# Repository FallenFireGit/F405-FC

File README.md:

# F405-FC

STM32F405 flight controller for 30.5 mm quadcopter stacks. 2–6S input, dual IMU, Betaflight and INAV targets. Every part is sourced from DigiKey.

| Top | Bottom |
|---|---|
|  |  |

> **Status: rev D, design complete, not yet built.** DRC and ERC are clean, and every review gate's major findings are fixed and re-reviewed. Nothing has been fabricated, powered or flashed yet. See [review/summary.md](review/summary.md) for open risks and the list of what wasn't verified.

## Specs

| | |
|---|---|
| MCU | STM32F405RGT6, 168 MHz, LQFP-64 |
| IMUs | ICM-42688-P + BMI270 (SPI1, separate CS and INT) |
| Barometer | BMP390 (I2C1) |
| Magnetometer | IIS2MDC (I2C1), plus external I2C on the GPS port |
| Blackbox | W25N01GV, 1 Gbit SPI NAND |
| Input | 2–6S, SMBJ26A TVS, VBAT/GND solder pads |
| Regulators | 2× LMR38020 synchronous buck (5 V, and 10 V switchable for VTX pit mode), LP38692 3.3 V, LP5907 low-noise 3.3 V for the IMUs |
| Video | HD digital VTX port (MSP DisplayPort OSD) on a JST-SH 6-pin, analog camera switch (TS5A3159A) between two cameras |
| Outputs | 8 motor/servo outputs (M1–M4 on the ESC connector support bidirectional DShot), WS2812 LED strip, buzzer |
| I/O | 6 UARTs, USB-C (USB 2.0 FS, ESD protected), JST-SH ESC 8-pin, GPS 6-pin, ELRS 4-pin |
| Board | 36 × 36 mm, 30.5 mm M3 mounting, 6 layers (solid GND on In1/In4), 1.6 mm |
| Assembly | Hand / hot-air with stencil, 0402 minimum, no BGA |

There's no analog OSD. The AT7456E has no DigiKey listing and the MAX7456 is obsolete, so OSD comes over MSP DisplayPort (see [D-01](design/decisions.md)).

## Repository layout

| Path | Contents |
|---|---|
| `kicad/` | KiCad 10 project: hierarchical schematic, board, design rules |
| `fab/` | JLCPCB Gerber/drill zip, stencil, placement (CPL) files |
| `bom/` | DigiKey BOM Manager CSV, costed BOM (~$173 for 2 boards plus spares), interactive HTML BOM |
| `docs/` | Schematic PDF, STEP, renders, Betaflight config, INAV target, [assembly and bring-up guide](docs/assembly_and_bringup.md) |
| `design/` | Requirements, pin map and DMA plan, power design, decision log |
| `review/` | Reports from each review gate (pin map, power, schematic, sourcing, footprints, placement, SI/PI, DFM, red team) |
| `gen/` | Python generators: circuit model → schematic → board, routing helpers, checks |
| `lib/` | Custom footprints |

## How it was made

The design was generated from a Python circuit model (`gen/`) into KiCad 10. It was routed with a mix of scripted critical routes and Freerouting. It then went through staged reviews, each done by independent agents told to assume mistakes exist and to cite evidence:

0. pin map and power
1. schematic
2. sourcing and footprints
3. placement
4. signal and power integrity
5. manufacturability
6. two red teams (first power-up and Betaflight bring-up)

Each gate looped through fixes and re-review until no blocking or major findings remained. The previous 4-layer rev C is kept on branch [`rev-c`](../../tree/rev-c); it isn't recommended.

## Before ordering

- Upload `bom/F405FC_digikey_bom.csv` to DigiKey's BOM Manager to confirm live stock and prices. Stock was checked only through dated web snapshots.
- Choose the JLCPCB 6-layer stackup and order **epoxy-filled, capped vias (POFV)**, since some vias are in or next to pads.
- Follow the bring-up guide: check the rails on a current-limited supply before fitting the MCU.

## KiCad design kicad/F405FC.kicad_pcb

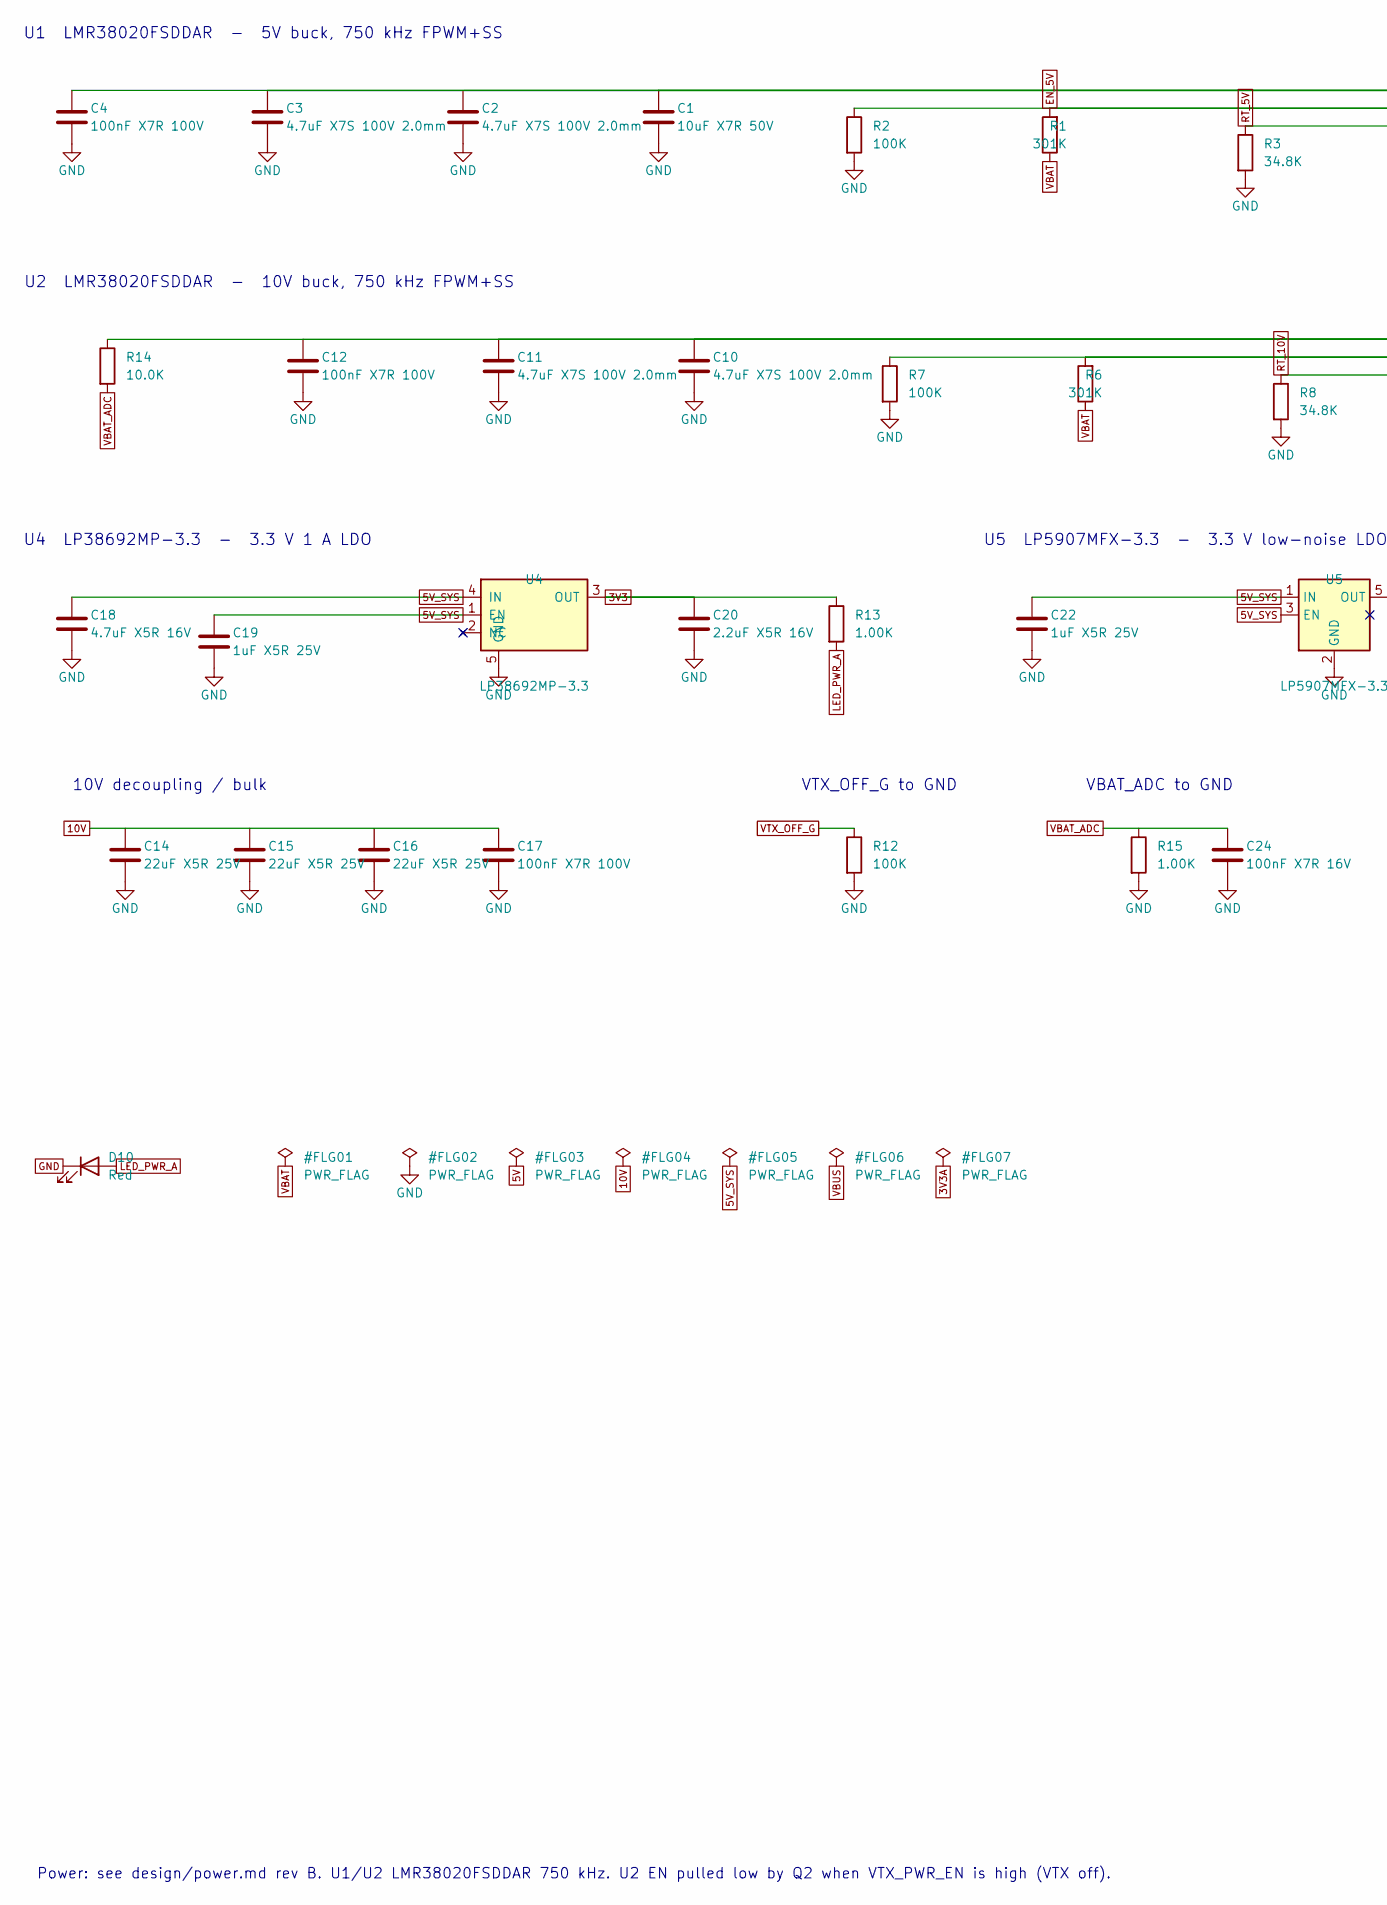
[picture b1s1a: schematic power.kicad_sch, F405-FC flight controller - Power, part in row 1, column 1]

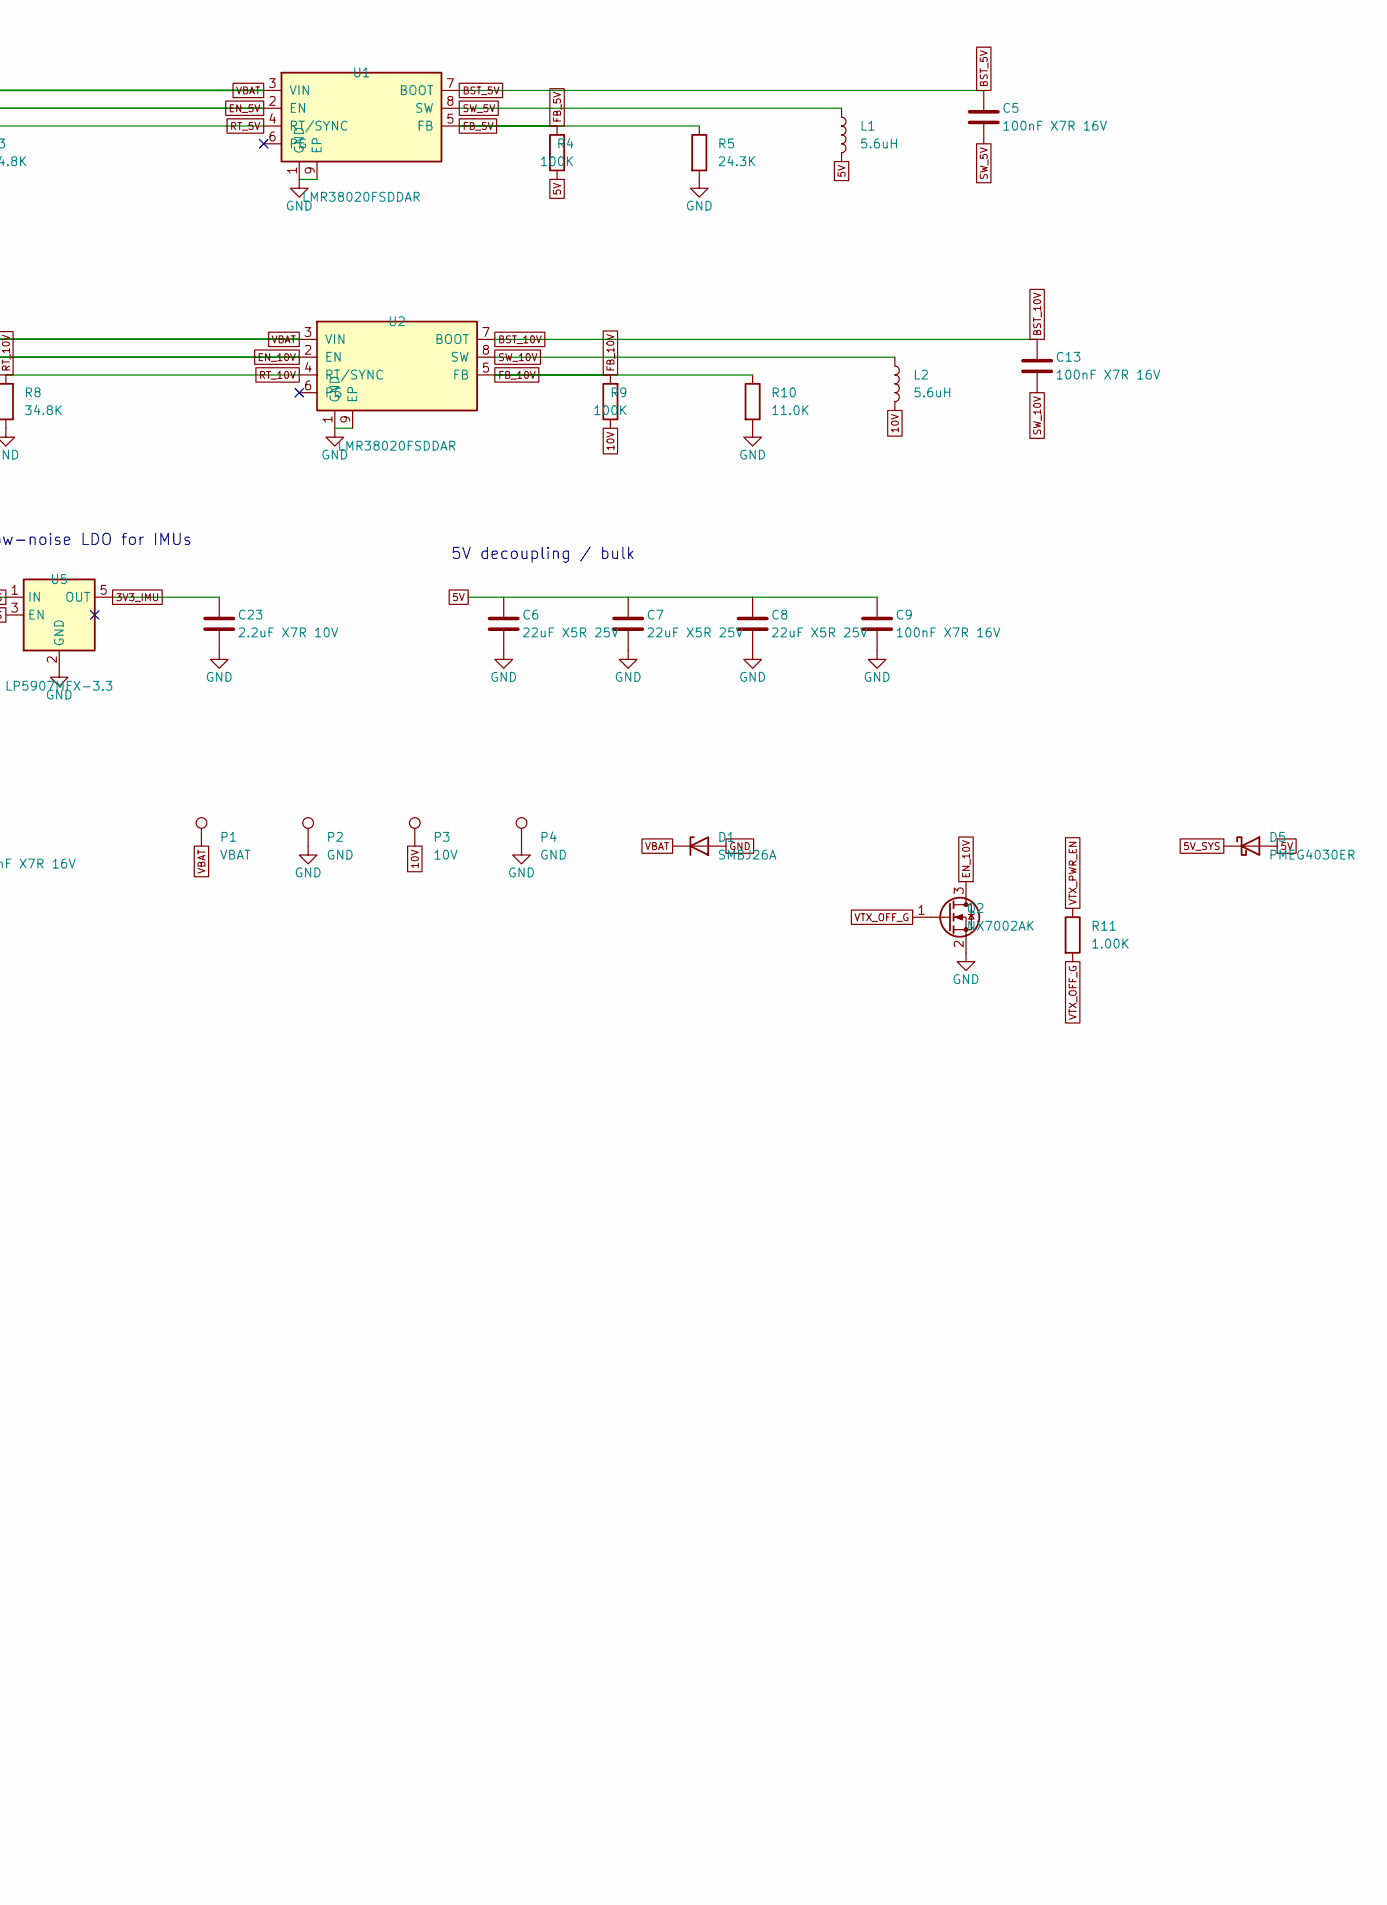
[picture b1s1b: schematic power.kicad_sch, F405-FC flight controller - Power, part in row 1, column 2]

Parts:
C1: 10uF X7R 50V; C_1210_3225Metric; MPN CL32B106KBJNNNE; DigiKey 1276-3387-1-ND
C2, C3, C10, C11: 4.7uF X7S 100V 2.0mm; C_1210_3225Metric; MPN C3225X7S2A475K200AB; DigiKey 445-6042-1-ND (verify: K200AB cut tape)
C4, C12, C17: 100nF X7R 100V; C_0603_1608Metric; MPN GRM188R72A104KA35D; DigiKey 490-3285-1-ND (verify)
C5, C9, C13, C24: 100nF X7R 16V; C_0402_1005Metric; MPN CL05B104KO5NNNC; DigiKey 1276-1001-1-ND
C6, C7, C8, C14, C15, C16: 22uF X5R 25V; C_1206_3216Metric; MPN CL31A226KAHNNNE; DigiKey 1276-3047-1-ND
C18: 4.7uF X5R 16V; C_0603_1608Metric; MPN CL10A475KO8NNNC; DigiKey 1276-1784-1-ND
C19, C22: 1uF X5R 25V; C_0603_1608Metric; MPN CL10A105KA8NNNC; DigiKey 1276-1102-1-ND (verify)
C20: 2.2uF X5R 16V; C_0603_1608Metric; MPN CL10A225KO8NNNC; DigiKey 1276-1040-1-ND
C23: 2.2uF X7R 10V; C_0603_1608Metric; MPN CL10B225KP8NNNC; DigiKey 1276-1134-1-ND
D1: SMBJ26A; D_SMB; MPN SMBJ26A; DigiKey SMBJ26ALFCT-ND
D5: PMEG4030ER; Nexperia_CFP3_SOD-123W; MPN PMEG4030ER,115; DigiKey 1727-5313-1-ND
D10: Red; LED_0603_1608Metric; MPN LTST-C191KRKT; DigiKey 160-1447-1-ND
L1, L2: 5.6uH; L_Wuerth_MAPI-4020; MPN 78438356056; DigiKey 732-11317-1-ND
P1: VBAT; Pad_SMD_2.5x4.0mm; MPN n/a (PCB pad); DigiKey n/a (PCB pad)
P2: GND; Pad_SMD_2.5x4.0mm; MPN n/a (PCB pad); DigiKey n/a (PCB pad)
P3: 10V; Pad_SMD_2.0x3.0mm; MPN n/a (PCB pad); DigiKey n/a (PCB pad)
P4: GND; Pad_SMD_2.0x3.0mm; MPN n/a (PCB pad); DigiKey n/a (PCB pad)
Q2: NX7002AK; SOT-23; MPN NX7002AK,215; DigiKey 1727-1289-1-ND
R1, R6: 301K; R_0603_1608Metric; MPN RC0603FR-07301KL; DigiKey 311-301KHRCT-ND
R2, R4, R7, R9, R12: 100K; R_0402_1005Metric; MPN RC0402FR-07100KL; DigiKey 311-100KLRCT-ND
R3, R8: 34.8K; R_0402_1005Metric; MPN ERJ-2RKF3482X; DigiKey P34.8KLCT-ND
R5: 24.3K; R_0402_1005Metric; MPN ERJ-2RKF2432X; DigiKey P24.3KLCT-ND
R10: 11.0K; R_0402_1005Metric; MPN RC0402FR-0711KL; DigiKey 311-11.0KLRCT-ND
R11, R13, R15: 1.00K; R_0402_1005Metric; MPN RC0402FR-071KL; DigiKey 311-1.00KLRCT-ND
R14: 10.0K; R_0603_1608Metric; MPN RC0603FR-0710KL; DigiKey 311-10.0KHRCT-ND
U1, U2: LMR38020FSDDAR; TI_HSOIC-8-1EP_3.9x4.9mm_P1.27mm_EP2.71x3.4mm_DDA; MPN LMR38020FSDDAR; DigiKey 296-LMR38020FSDDARCT-ND (verify)
U4: LP38692MP-3.3; SOT-223-5; MPN LP38692MP-3.3/NOPB; DigiKey LP38692MP-3.3/NOPBCT-ND
U5: LP5907MFX-3.3; SOT-23-5; MPN LP5907MFX-3.3/NOPB; DigiKey 296-38557-1-ND

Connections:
3V3: C20.1, R13.1, U4.3 (OUT); also elsewhere on the board
3V3_IMU: C23.1, U5.5 (OUT); also elsewhere on the board
5V: C6.1, C7.1, C8.1, C9.1, D5.2 (A), L1.2, R4.1; also elsewhere on the board
5V_SYS: C18.1, C19.1, C22.1, D5.1 (K), U4.1 (EN), U4.4 (IN), U5.1 (IN), U5.3 (EN); also elsewhere on the board
10V: C14.1, C15.1, C16.1, C17.1, L2.2, P3.1, R9.1; also elsewhere on the board
BST_5V: C5.1, U1.7 (BOOT)
BST_10V: C13.1, U2.7 (BOOT)
EN_5V: R1.2, R2.1, U1.2 (EN)
EN_10V: Q2.3 (D), R6.2, R7.1, U2.2 (EN)
FB_5V: R4.2, R5.1, U1.5 (FB)
FB_10V: R9.2, R10.1, U2.5 (FB)
GND: C1.2, C2.2, C3.2, C4.2, C6.2, C7.2, C8.2, C9.2, C10.2, C11.2, C12.2, C14.2, C15.2, C16.2, C17.2, C18.2, C19.2, C20.2, C22.2, C23.2, C24.2, D1.2 (A), D10.1 (K), P2.1, P4.1, Q2.2 (S), R2.2, R3.2, R5.2, R7.2, R8.2, R10.2, R12.2, R15.2, U1.1 (GND), U1.9 (EP), U2.1 (GND), U2.9 (EP), U4.5 (GND), U5.2 (GND); also elsewhere on the board
LED_PWR_A: D10.2 (A), R13.2
RT_5V: R3.1, U1.4 (RT/SYNC)
RT_10V: R8.1, U2.4 (RT/SYNC)
SW_5V: C5.2, L1.1, U1.8 (SW)
SW_10V: C13.2, L2.1, U2.8 (SW)
VBAT: C1.1, C2.1, C3.1, C4.1, C10.1, C11.1, C12.1, D1.1 (K), P1.1, R1.1, R6.1, R14.1, U1.3 (VIN), U2.3 (VIN); also elsewhere on the board
VBAT_ADC: C24.1, R14.2, R15.1; also elsewhere on the board
VTX_OFF_G: Q2.1 (G), R11.2, R12.1
VTX_PWR_EN: R11.1; also elsewhere on the board

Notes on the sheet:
U1 LMR38020FSDDAR - 5V buck, 750 kHz FPWM+SS
U2 LMR38020FSDDAR - 10V buck, 750 kHz FPWM+SS
U4 LP38692MP-3.3 - 3.3 V 1 A LDO
U5 LP5907MFX-3.3 - 3.3 V low-noise LDO for IMUs
5V decoupling / bulk
10V decoupling / bulk
VTX_OFF_G to GND
VBAT_ADC to GND
Power: see design/power.md rev B. U1/U2 LMR38020FSDDAR 750 kHz. U2 EN pulled low by Q2 when VTX_PWR_EN is high (VTX off).

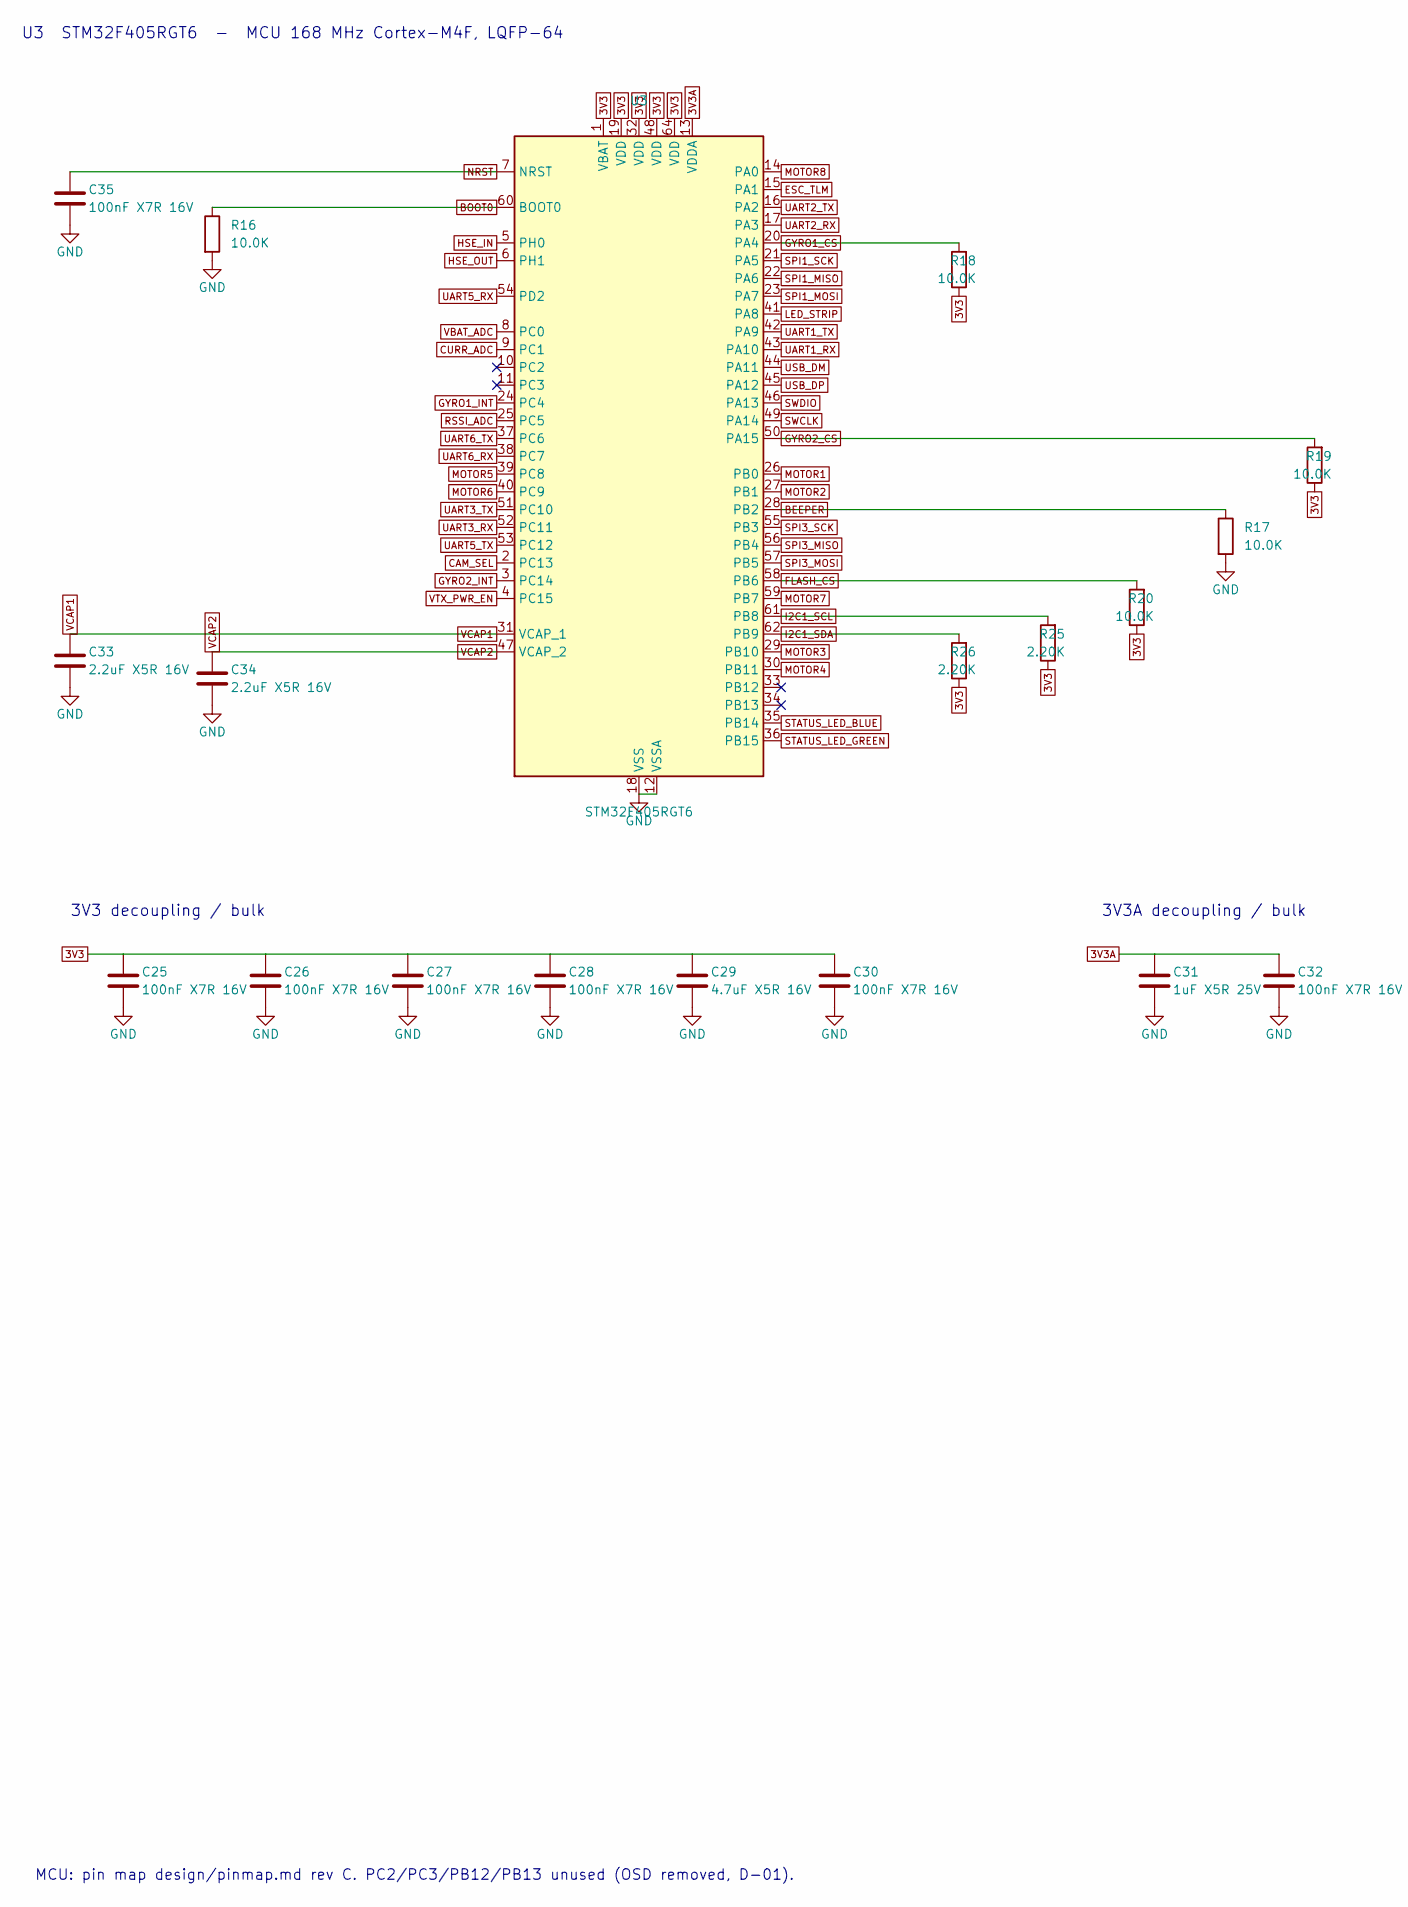
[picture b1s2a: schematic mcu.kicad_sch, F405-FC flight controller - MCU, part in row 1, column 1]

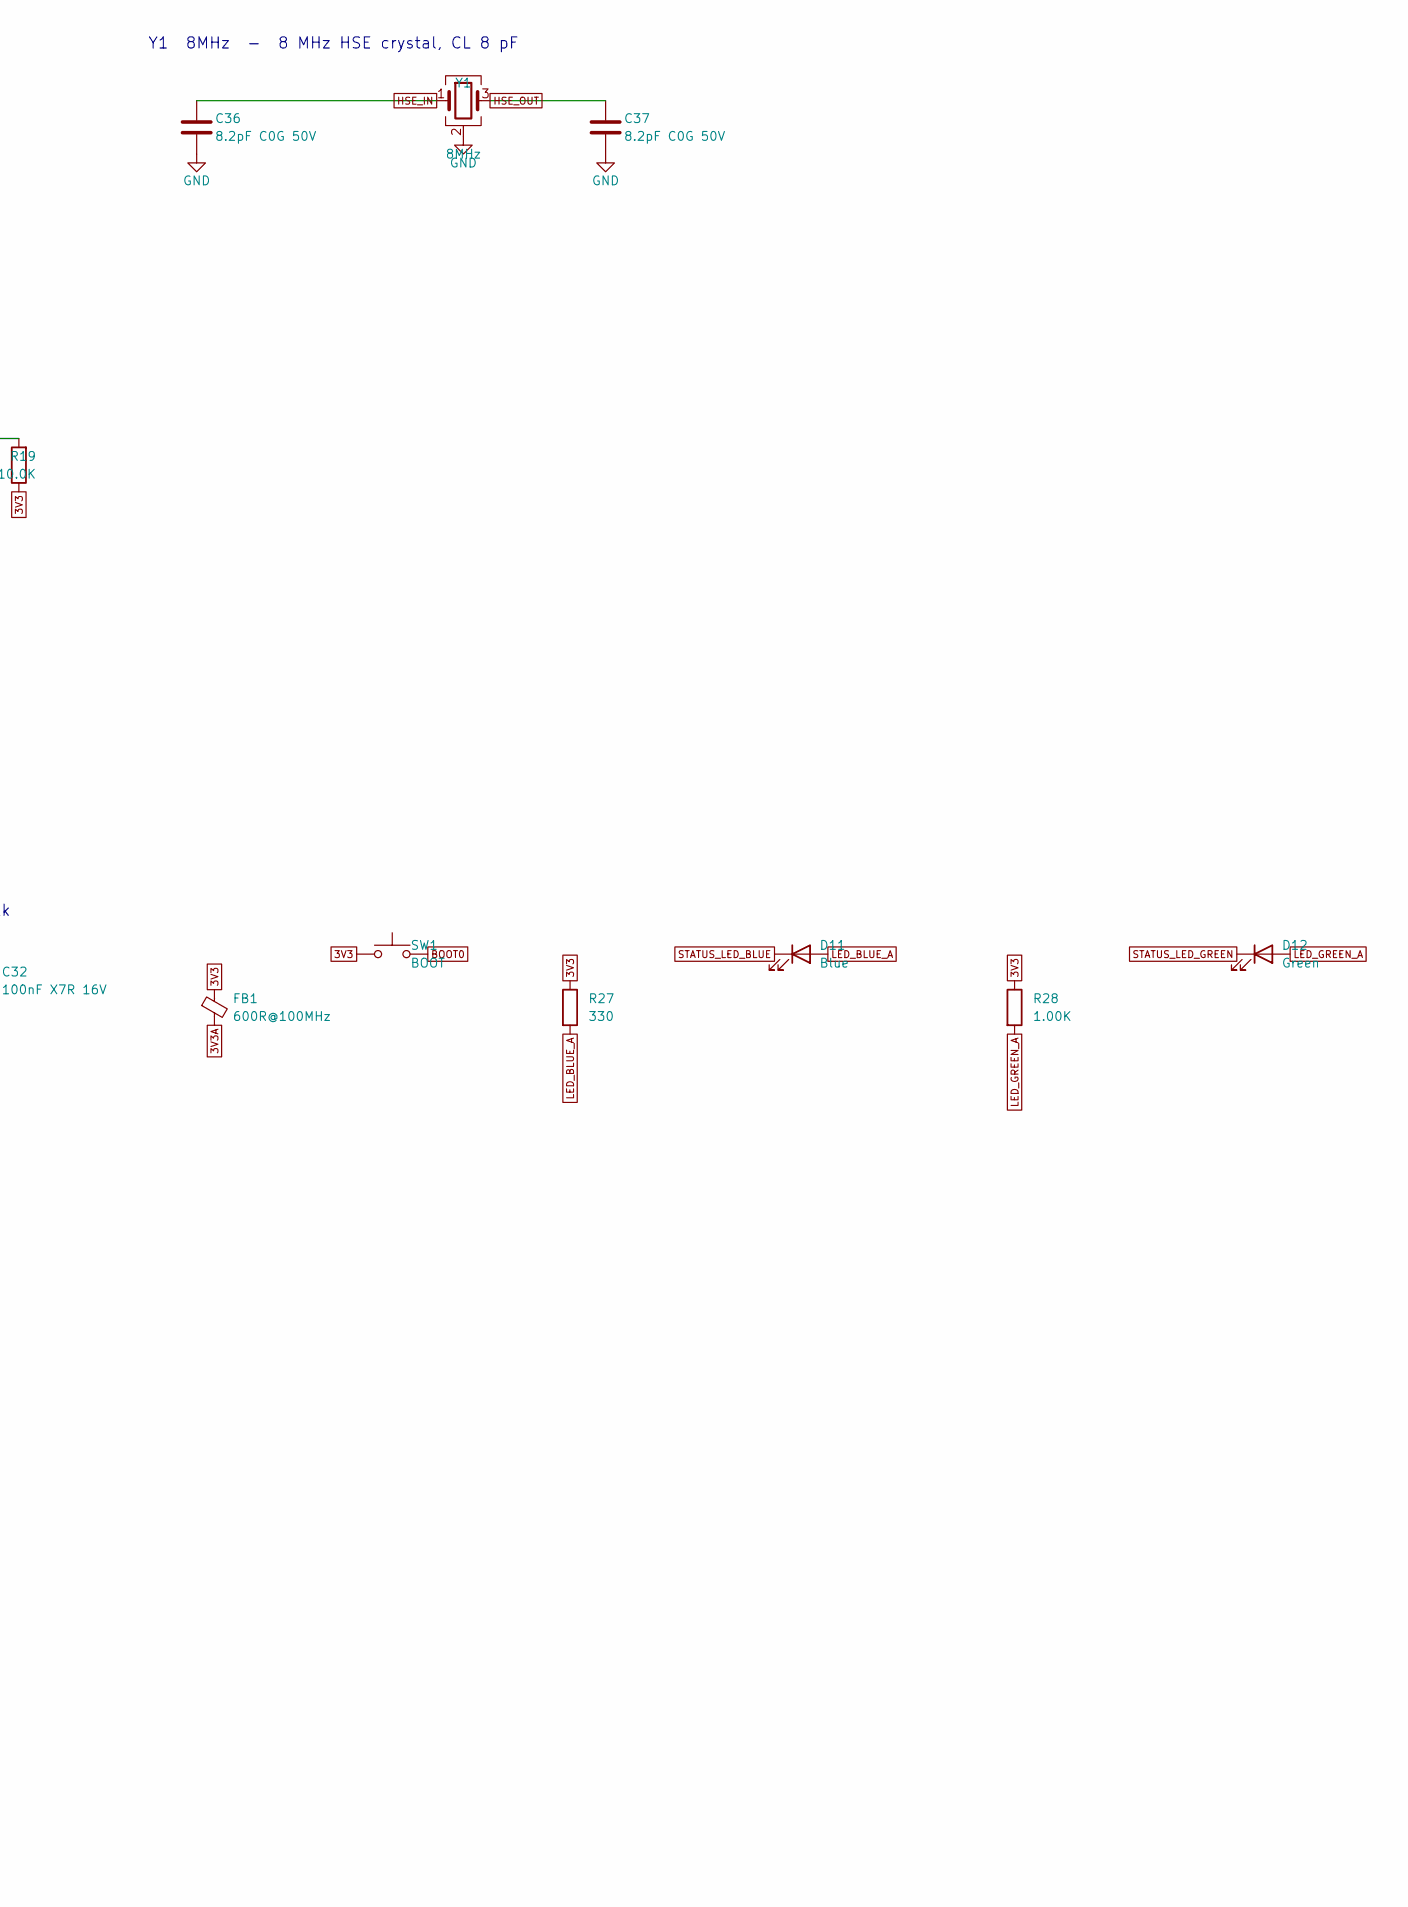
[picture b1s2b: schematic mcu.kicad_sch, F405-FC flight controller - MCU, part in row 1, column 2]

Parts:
C25, C26, C27, C28, C30, C32, C35: 100nF X7R 16V; C_0402_1005Metric; MPN CL05B104KO5NNNC; DigiKey 1276-1001-1-ND
C29: 4.7uF X5R 16V; C_0603_1608Metric; MPN CL10A475KO8NNNC; DigiKey 1276-1784-1-ND
C31: 1uF X5R 25V; C_0603_1608Metric; MPN CL10A105KA8NNNC; DigiKey 1276-1102-1-ND (verify)
C33, C34: 2.2uF X5R 16V; C_0603_1608Metric; MPN CL10A225KO8NNNC; DigiKey 1276-1040-1-ND
C36, C37: 8.2pF C0G 50V; C_0402_1005Metric; MPN C0402C829C5GACTU; DigiKey 399-C0402C829C5GACTUCT-ND
D11: Blue; LED_0603_1608Metric; MPN LTST-C191TBKT; DigiKey 160-1647-1-ND
D12: Green; LED_0603_1608Metric; MPN LTST-C191KGKT; DigiKey 160-1446-1-ND
FB1: 600R@100MHz; L_0603_1608Metric; MPN BLM18KG601SN1D; DigiKey 490-5258-1-ND
R16, R17, R18, R19, R20: 10.0K; R_0402_1005Metric; MPN RC0402FR-0710KL; DigiKey 311-10.0KLRCT-ND
R25, R26: 2.20K; R_0402_1005Metric; MPN RC0402FR-072K2L; DigiKey 311-2.20KLRCT-ND
R27: 330; R_0402_1005Metric; MPN RC0402FR-07330RL; DigiKey 311-330LRCT-ND
R28: 1.00K; R_0402_1005Metric; MPN RC0402FR-071KL; DigiKey 311-1.00KLRCT-ND
SW1: BOOT; SW_SPST_PTS810; MPN PTS810 SJM 250 SMTR LFS; DigiKey CKN10502CT-ND
U3: STM32F405RGT6; LQFP-64_10x10mm_P0.5mm; MPN STM32F405RGT6; DigiKey 497-11767-ND
Y1: 8MHz; Crystal_SMD_3225-4Pin_3.2x2.5mm; MPN ECS-80-8-33-JEN-TR3; DigiKey 50-ECS-80-8-33-JEN-TR3CT-ND

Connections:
3V3: C25.1, C26.1, C27.1, C28.1, C29.1, C30.1, FB1.1, R18.1, R19.1, R20.1, R25.1, R26.1, R27.1, R28.1, SW1.1, U3.1 (VBAT), U3.19 (VDD), U3.32 (VDD), U3.48 (VDD), U3.64 (VDD); also elsewhere on the board
3V3A: C31.1, C32.1, FB1.2, U3.13 (VDDA)
BEEPER: R17.1, U3.28 (PB2); also elsewhere on the board
BOOT0: R16.1, SW1.2, U3.60 (BOOT0)
CAM_SEL: U3.2 (PC13); also elsewhere on the board
CURR_ADC: U3.9 (PC1); also elsewhere on the board
ESC_TLM: U3.15 (PA1); also elsewhere on the board
FLASH_CS: R20.2, U3.58 (PB6); also elsewhere on the board
GND: C25.2, C26.2, C27.2, C28.2, C29.2, C30.2, C31.2, C32.2, C33.2, C34.2, C35.2, C36.2, C37.2, R16.2, R17.2, U3.12 (VSSA), U3.18 (VSS), U3.63 (VSS), Y1.2 (G), Y1.4 (G); also elsewhere on the board
GYRO1_CS: R18.2, U3.20 (PA4); also elsewhere on the board
GYRO1_INT: U3.24 (PC4); also elsewhere on the board
GYRO2_CS: R19.2, U3.50 (PA15); also elsewhere on the board
GYRO2_INT: U3.3 (PC14); also elsewhere on the board
HSE_IN: C36.1, U3.5 (PH0), Y1.1
HSE_OUT: C37.1, U3.6 (PH1), Y1.3
I2C1_SCL: R25.2, U3.61 (PB8); also elsewhere on the board
I2C1_SDA: R26.2, U3.62 (PB9); also elsewhere on the board
LED_BLUE_A: D11.2 (A), R27.2
LED_GREEN_A: D12.2 (A), R28.2
LED_STRIP: U3.41 (PA8); also elsewhere on the board
MOTOR1: U3.26 (PB0); also elsewhere on the board
MOTOR2: U3.27 (PB1); also elsewhere on the board
MOTOR3: U3.29 (PB10); also elsewhere on the board
MOTOR4: U3.30 (PB11); also elsewhere on the board
MOTOR5: U3.39 (PC8); also elsewhere on the board
MOTOR6: U3.40 (PC9); also elsewhere on the board
MOTOR7: U3.59 (PB7); also elsewhere on the board
MOTOR8: U3.14 (PA0); also elsewhere on the board
NRST: C35.1, U3.7 (NRST); also elsewhere on the board
RSSI_ADC: U3.25 (PC5); also elsewhere on the board
SPI1_MISO: U3.22 (PA6); also elsewhere on the board
SPI1_MOSI: U3.23 (PA7); also elsewhere on the board
SPI1_SCK: U3.21 (PA5); also elsewhere on the board
SPI3_MISO: U3.56 (PB4); also elsewhere on the board
SPI3_MOSI: U3.57 (PB5); also elsewhere on the board
SPI3_SCK: U3.55 (PB3); also elsewhere on the board
STATUS_LED_BLUE: D11.1 (K), U3.35 (PB14)
STATUS_LED_GREEN: D12.1 (K), U3.36 (PB15)
SWCLK: U3.49 (PA14); also elsewhere on the board
SWDIO: U3.46 (PA13); also elsewhere on the board
UART1_RX: U3.43 (PA10); also elsewhere on the board
UART1_TX: U3.42 (PA9); also elsewhere on the board
UART2_RX: U3.17 (PA3); also elsewhere on the board
UART2_TX: U3.16 (PA2); also elsewhere on the board
UART3_RX: U3.52 (PC11); also elsewhere on the board
UART3_TX: U3.51 (PC10); also elsewhere on the board
UART5_RX: U3.54 (PD2); also elsewhere on the board
UART5_TX: U3.53 (PC12); also elsewhere on the board
UART6_RX: U3.38 (PC7); also elsewhere on the board
UART6_TX: U3.37 (PC6); also elsewhere on the board
USB_DM: U3.44 (PA11); also elsewhere on the board
USB_DP: U3.45 (PA12); also elsewhere on the board
VBAT_ADC: U3.8 (PC0); also elsewhere on the board
VCAP1: C33.1, U3.31 (VCAP_1)
VCAP2: C34.1, U3.47 (VCAP_2)
VTX_PWR_EN: U3.4 (PC15); also elsewhere on the board

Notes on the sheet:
U3 STM32F405RGT6 - MCU 168 MHz Cortex-M4F, LQFP-64
Y1 8MHz - 8 MHz HSE crystal, CL 8 pF
3V3 decoupling / bulk
3V3A decoupling / bulk
MCU: pin map design/pinmap.md rev C. PC2/PC3/PB12/PB13 unused (OSD removed, D-01).

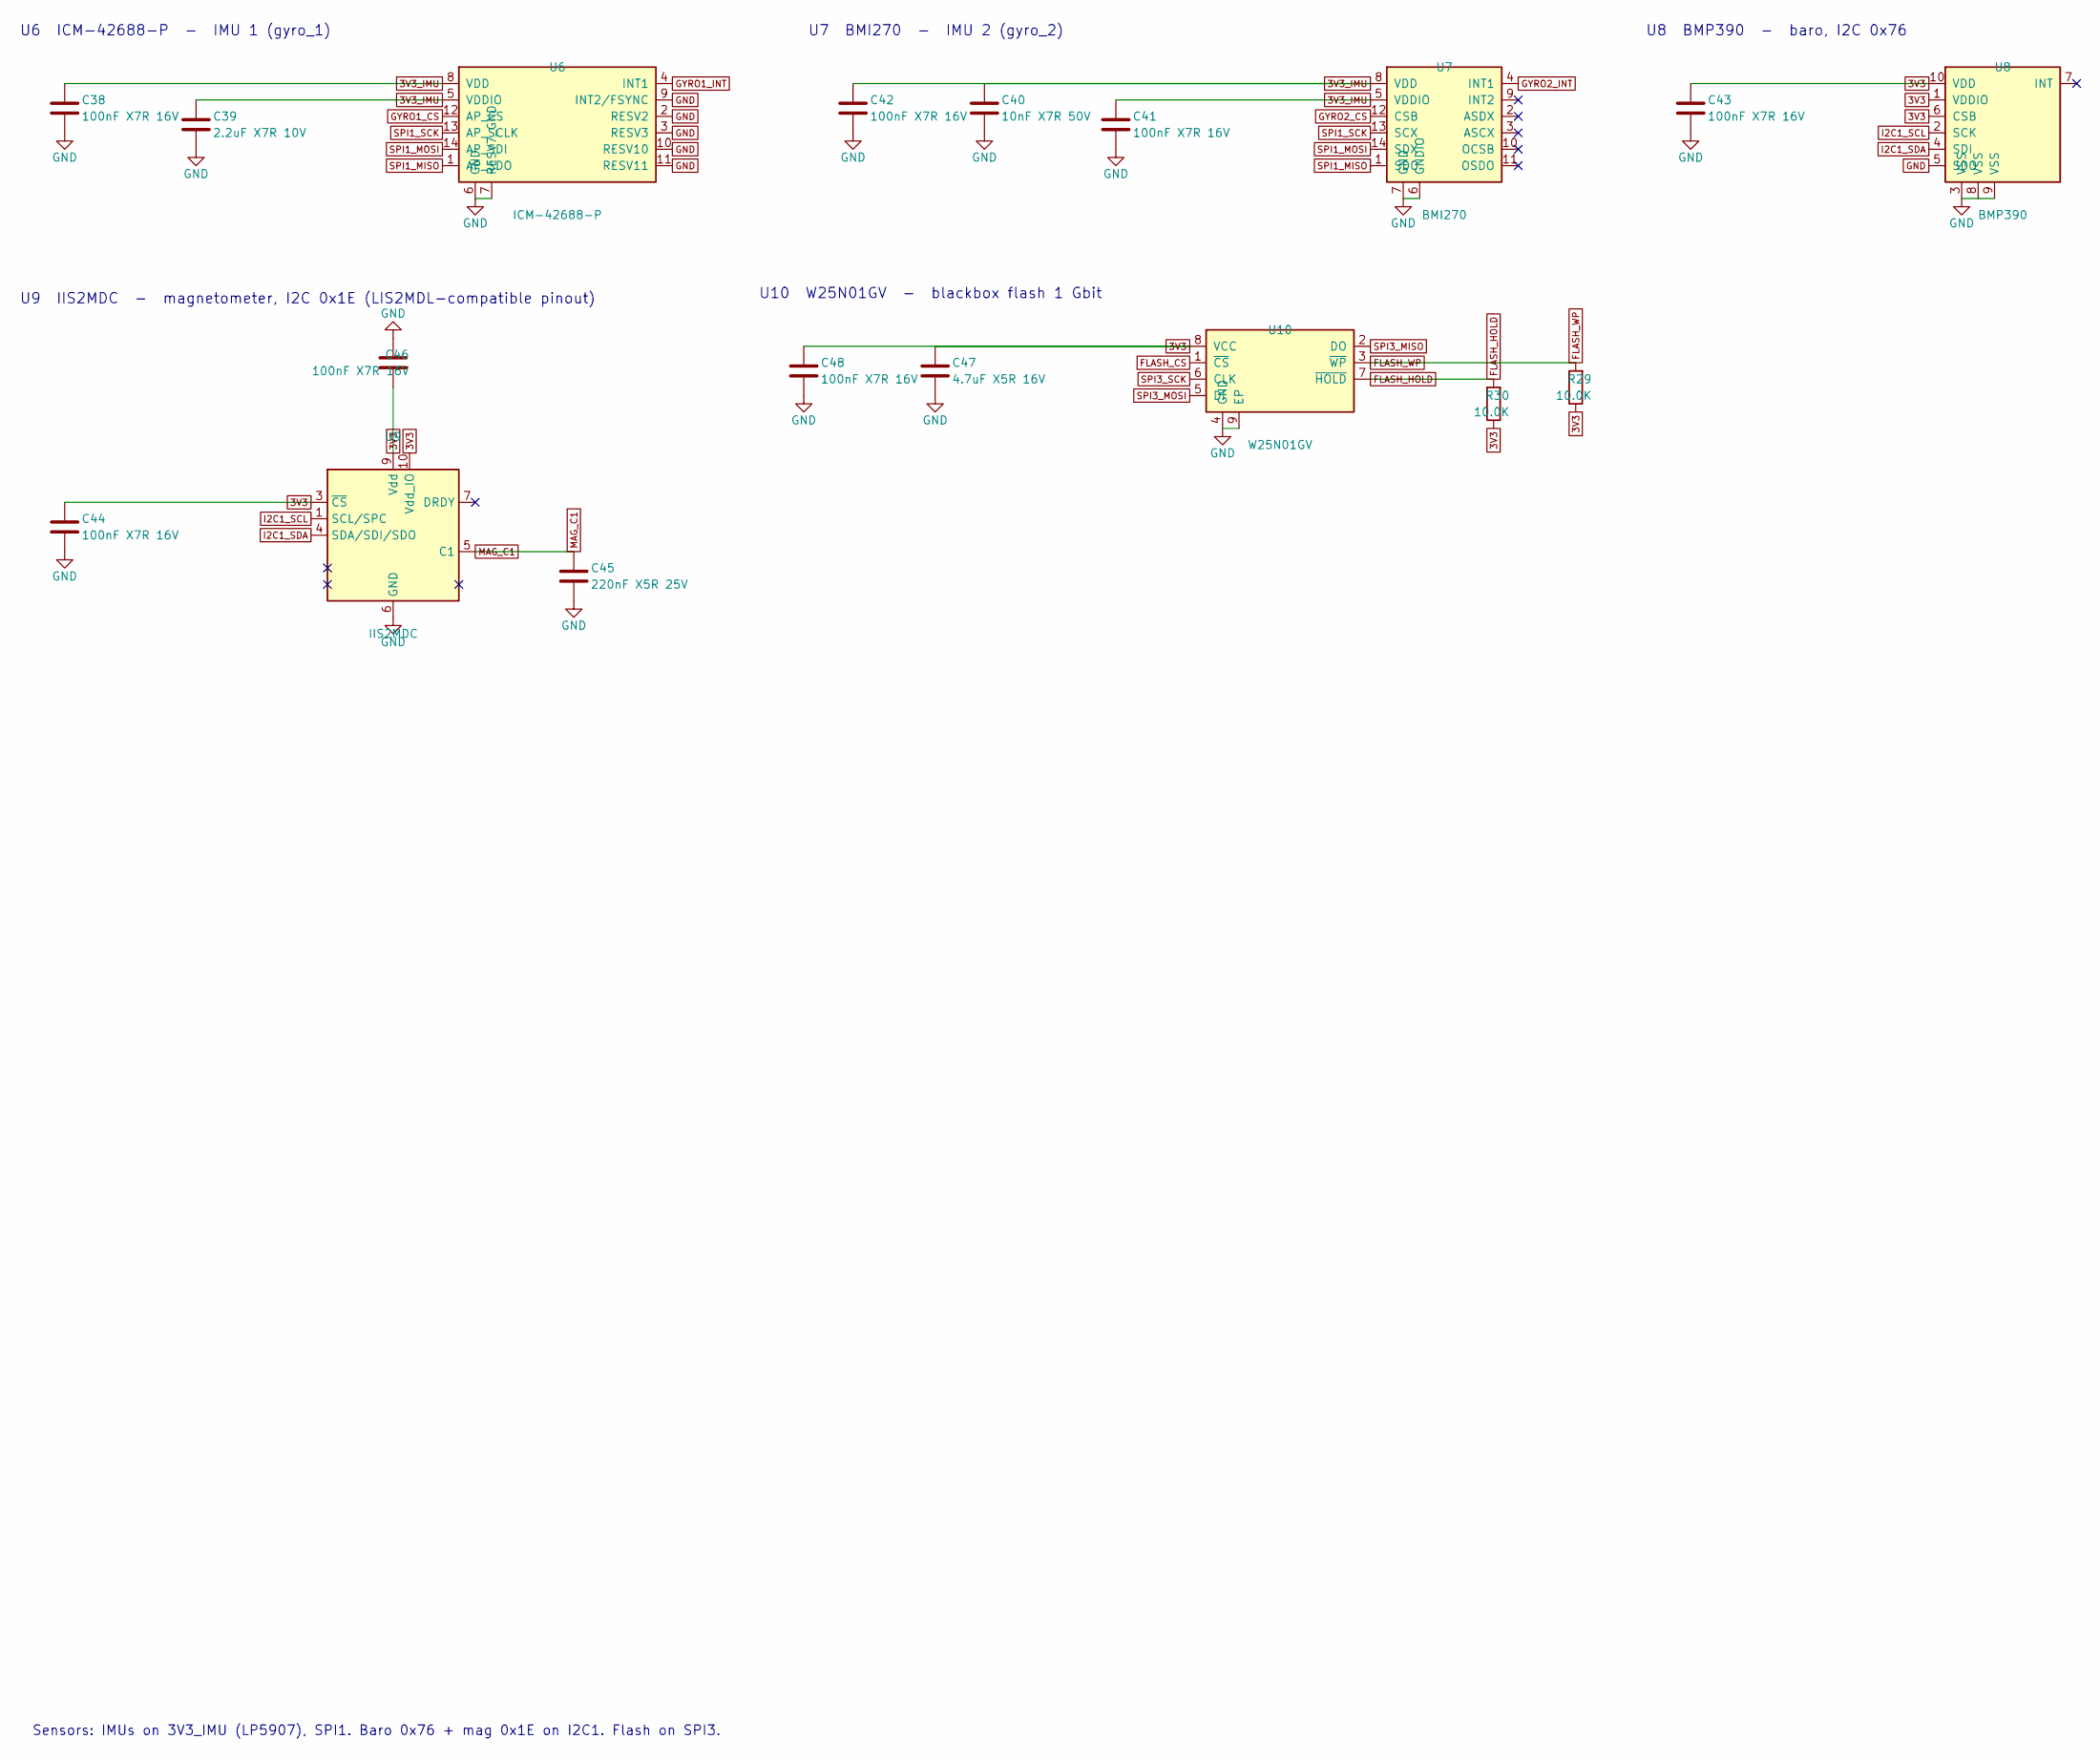
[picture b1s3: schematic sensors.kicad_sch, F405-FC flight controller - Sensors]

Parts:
C38, C41, C42, C43, C44, C46, C48: 100nF X7R 16V; C_0402_1005Metric; MPN CL05B104KO5NNNC; DigiKey 1276-1001-1-ND
C39: 2.2uF X7R 10V; C_0603_1608Metric; MPN CL10B225KP8NNNC; DigiKey 1276-1134-1-ND
C40: 10nF X7R 50V; C_0402_1005Metric; MPN CL05B103KB5NNNC; DigiKey 1276-1028-1-ND
C45: 220nF X5R 25V; C_0402_1005Metric; MPN CL05A224KA5NNNC; DigiKey 1276-1455-1-ND
C47: 4.7uF X5R 16V; C_0603_1608Metric; MPN CL10A475KO8NNNC; DigiKey 1276-1784-1-ND
R29, R30: 10.0K; R_0402_1005Metric; MPN RC0402FR-0710KL; DigiKey 311-10.0KLRCT-ND
U6: ICM-42688-P; LGA-14_3x2.5mm_P0.5mm_LayoutBorder3x4y; MPN ICM-42688-P; DigiKey 1428-ICM-42688-PCT-ND
U7: BMI270; Bosch_LGA-14_3x2.5mm_P0.5mm_BMI270; MPN BMI270; DigiKey 828-1091-1-ND
U8: BMP390; Bosch_LGA-10_2x2mm_P0.5mm_BMP390; MPN BMP390; DigiKey 828-BMP390CT-ND
U9: IIS2MDC; LGA-12_2x2mm_P0.5mm; MPN IIS2MDCTR; DigiKey 497-17728-1-ND
U10: W25N01GV; WSON-8-1EP_8x6mm_P1.27mm_EP3.4x4.3mm; MPN W25N01GVZEIG TR; DigiKey 256-W25N01GVZEIGTRCT-ND

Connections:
3V3: C43.1, C44.1, C46.1, C47.1, C48.1, R29.1, R30.1, U8.1 (VDDIO), U8.6 (CSB), U8.10 (VDD), U9.3 (~CS), U9.9 (Vdd), U9.10 (Vdd_IO), U10.8 (VCC); also elsewhere on the board
3V3_IMU: C38.1, C39.1, C40.1, C41.1, C42.1, U6.5 (VDDIO), U6.8 (VDD), U7.5 (VDDIO), U7.8 (VDD); also elsewhere on the board
FLASH_CS: U10.1 (~CS); also elsewhere on the board
FLASH_HOLD: R30.2, U10.7 (~HOLD)
FLASH_WP: R29.2, U10.3 (~WP)
GND: C38.2, C39.2, C40.2, C41.2, C42.2, C43.2, C44.2, C45.2, C46.2, C47.2, C48.2, U6.2 (RESV2), U6.3 (RESV3), U6.6 (GND), U6.7 (RESV7_GND), U6.9 (INT2/FSYNC), U6.10 (RESV10), U6.11 (RESV11), U7.6 (GNDIO), U7.7 (GND), U8.3 (VSS), U8.5 (SDO), U8.8 (VSS), U8.9 (VSS), U9.6 (GND), U9.8 (GND), U10.4 (GND), U10.9 (EP); also elsewhere on the board
GYRO1_CS: U6.12 (AP_CS); also elsewhere on the board
GYRO1_INT: U6.4 (INT1); also elsewhere on the board
GYRO2_CS: U7.12 (CSB); also elsewhere on the board
GYRO2_INT: U7.4 (INT1); also elsewhere on the board
I2C1_SCL: U8.2 (SCK), U9.1 (SCL/SPC); also elsewhere on the board
I2C1_SDA: U8.4 (SDI), U9.4 (SDA/SDI/SDO); also elsewhere on the board
MAG_C1: C45.1, U9.5 (C1)
SPI1_MISO: U6.1 (AP_SDO), U7.1 (SDO); also elsewhere on the board
SPI1_MOSI: U6.14 (AP_SDI), U7.14 (SDX); also elsewhere on the board
SPI1_SCK: U6.13 (AP_SCLK), U7.13 (SCX); also elsewhere on the board
SPI3_MISO: U10.2 (DO); also elsewhere on the board
SPI3_MOSI: U10.5 (DI); also elsewhere on the board
SPI3_SCK: U10.6 (CLK); also elsewhere on the board

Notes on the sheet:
U6 ICM-42688-P - IMU 1 (gyro_1)
U7 BMI270 - IMU 2 (gyro_2)
U8 BMP390 - baro, I2C 0x76
U9 IIS2MDC - magnetometer, I2C 0x1E (LIS2MDL-compatible pinout)
U10 W25N01GV - blackbox flash 1 Gbit
Sensors: IMUs on 3V3_IMU (LP5907), SPI1. Baro 0x76 + mag 0x1E on I2C1. Flash on SPI3.
